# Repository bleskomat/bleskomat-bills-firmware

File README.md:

# bleskomat-bills-firmware

The Bleskomat Bills ATM is an offline Bitcoin Lightning Network ATM which accepts fiat bank notes and pays-out bitcoin. It's a great educational tool to give others a practical first experience with Bitcoin's Lightning Network.

You can buy the [Bleskomat Bills ATM](https://shop.bleskomat.com/product/bleskomat-bills-atm/) from the official Bleskomat shop. Alternatively, you can find all the components and equipment needed and build your own.

The Bleskomat Bills ATM must be paired with a server to facilitate Lightning Network payments on its behalf; see the options below:
* [Bleskomat Platform](https://platform.bleskomat.com) - non-custodial, requires a monthly subscription
* [bleskomat-server](https://github.com/bleskomat/bleskomat-server) - non-custodial, open-source, self-hosted solution
* [lnbits](https://github.com/lnbits/lnbits-legend) via the Bleskomat extension - open-source, self-hosted and possible to use custodial instances hosted by others; public instances of lnbits:
	* [legend.lnbits.com](https://legend.lnbits.com) - unstable, don't leave funds on this instance for very long

The rest of this document details the hardware and software requirements, how to build the hardware yourself, and instructions for compiling and uploading the firmware from source.

* [Requirements](#requirements)
	* [Hardware Requirements](#hardware-requirements)
	* [Software Requirements](#software-requirements)
* [Building the Hardware Device](#building-the-hardware-device)
	* [Prepare the breadboards](#prepare-the-breadboards)
		* [ESP32 devkit pinout](#esp32-devkit-pinout)
	* [Wiring the Power Supply](#wiring-the-power-supply)
		* [Optionally power the ESP32 devkit via 5V pin](#optionally-power-the-esp32-devkit-via-5v-pin)
	* [Wiring the E-Paper Module](#wiring-the-e-paper-module)
	* [Wiring the Button](#wiring-the-button)
	* [Wiring the Bill Acceptor](#wiring-the-bill-acceptor)
* [Installing Libraries and Dependencies](#installing-libraries-and-dependencies)
* [Compiling and Uploading to Device](#compiling-and-uploading-to-device)
* [Generate Font Header Files](#generate-font-header-files)
* [Configure Bill Acceptor](#configure-bill-acceptor)
* [Configuring the Device](#configuring-the-device)
	* [List of Configuration Options](#list-of-configuration-options)
	* [Browser-Based Configuration Tool](#browser-based-configuration-tool)
	* [Command-Line Configuration Tool](#command-line-configuration-tool)
	* [Hard-Coded Configuration](#hard-coded-configuration)
* [Changelog](#changelog)
* [Support](#support)
* [License](#license)
* [Trademark](#trademark)

## Requirements

This section includes information about the software and hardware requirements needed to build this project.

### Hardware Requirements

The following list includes all the parts needed to build the commercial Bleskomat ATM. The list includes direct links to suppliers of each part.

Basic components/equipment needed to build your own Bleskomat Bills ATM:
* 2 x breadboard (400-pin)
* Jumper wires (M-M)
* Jumper wires (M-F)
* ESP32 Devkit
* NV10 Bill Acceptor from Innovative Technologies
* WaveShare 4.2 inch E-Paper Module (b/w)
* Button
* 10k ohm resistor
* DC 5.5/2.1 mm DIP adapter
* 12V DC power adaptor (1.5A < 3A)
* Standard USB to micro USB cable

Optional components/equipment:
* Soldering iron
* 2.54 mm pins
* To power the ESP32 devkit from the 12V DC power supply:
	* XL4005 step-down converter
	* USB (F) adapter
	* Alternatively, you could use a USB car charger which includes both a step-down converter and USB (F) output

### Software Requirements

* [make](https://www.gnu.org/software/make/)
* [PlatformIO Core (CLI)](https://docs.platformio.org/en/latest/core/)
	* Version 6 or newer
	* Only the CLI ("Core") is required

## Building the Hardware Device

Before proceeding, be sure that you have all the project's [hardware requirements](#hardware-requirements).

### Prepare the breadboards

One breadboard is not large enough to accommodate all the pins of the ESP32 devkit due to the width of the devkit. This is why we recommend to connect two breadboards together.

Remove one of the power rails from one of the breadboards. Use the notches on the sides of the breadboards to connect them together length-wise.

Insert the ESP32 devkit into the pin holes of the new, combined breadboard.

Familiarize yourself with the ESP32 devkit's pinout reference below.

#### ESP32 devkit pinout

### Wiring the Power Supply

The first step to building the device is wiring the power supply. If already plugged in, __unplug__ the 12V DC power supply now. Connect the DC 5.5/2.1 end of the power supply to the DIP adapter. The positive (+) pins should be the power pins and the negative (-) pins should be the ground. You can use your multimeter to check in case you want to be extra safe:
* Plug-in the power supply to electricity
* Turn on your multimeter and set it to measure voltage in the appropriate range (probably 20V)
* Touch the __red__ lead of your multimeter to one of the positive pins
* Touch the __black__ lead of your multimeter to one of the negative pins
* If you see a negative voltage reading, swap the leads between the two wires
* The pin touched by the __black__ lead is the ground ("GND")
* The pin touched by the __red__ lead is the hot wire ("DC12V")
* Unplug the power supply again

Use a pair of M-F jumper wires to connect the DC 5.5/2.1 DIP adapter to one of the breadboard's power rails. Negative to negative, positive to positive. This rail will be your 12V DC power (positive) and the common ground (negative).

#### Optionally power the ESP32 devkit via 5V pin

If you'd like to make your Bleskomat build a little bit more portable, you can power the ESP32 devkit via its 5V pin. To do this you will need the XL4005 (or equivalent) step-down converter and the USB (F) adapter. Note that powering the ESP32 devkit via its micro USB port requires a regulated voltage of approximately 5V.

It's also possible to use a USB car charger in case you have an extra one lying around.

Connect the step-down converter's input pins to the 12V DC power rail and common ground using (M-F) jumper wires. Use a multimeter to measure the voltage at the out pins. In the case of the XL4005, use a small screwdriver to turn the screw on the little blue box. Turning the screw counter clockwise should lower the voltage, turning it the opposite direction should increase the voltage. Once you have the voltage set to 5V, connect the out pins to the center power rails of the breadboard. This will be your 5V DC power rail.

Use a soldering iron to solder four 2.54 mm pins to the USB (F) DIP adapter. Insert the pins directly into the breadboard wherever you have space available. Using (M-M) jumper wires, connect the negative and positive pins of the USB (F) DIP adapter to the 5V DC power rail.

Connect the negative pin of the 5V DC power rail to the negative of the 12V DC power rail to ensure that they share a common ground. This is important because without a common ground shared between the coin acceptor and ESP32 devkit, the ESP32 will not receive a clean signal from the coin acceptor.

Use a standard USB to micro USB cable to connect the USB (F) DIP adapter to the ESP32 devkit.

There are other options when powering the ESP32 - e.g via the 3.3V pin or the 5V/VIN pin. You should __never__ power the ESP32 via more than one of these options at the same time. For example, do not power the ESP32 via its 3.3V pin while also connecting the ESP32 via USB to your computer. This can damage the ESP32 and possibly also your computer.

### Wiring the E-Paper Module

Connect the E-Paper display module to the ESP32 using the following table as a guide:

| ESP32 | E-Paper Display Module |
|-------|------------------------|
| D25   | BUSY                   |
| D26   | RST                    |
| D27   | DC                     |
| D15   | CS                     |
| D13   | CLK                    |
| D14   | DIN                    |
| GND   | GND                    |
| 3.3V  | VCC                    |

Refer to the [ESP32 devkit pinout](#esp32-devkit-pinout) for help identifying the pins on your ESP32.

### Wiring the Button

Insert button pins into the breadboard wherever you have space available. Typically, its best to place the button at the center of a breadboard (over the gap).

Connect the button using the following table as a guide:

| ESP32    | Button    |
|----------|-----------|
| VIN (V5) | left pin  |
| GPIO33   | right pin |

Connect the right pin of the button to GND with a 10k ohm resistor.

Refer to the [ESP32 devkit pinout](#esp32-devkit-pinout) for help identifying the pins on your ESP32.

### Wiring the Bill Acceptor

This project supports the NV10 (USB+) and NV9 bill acceptors. The SIO protocol is used to communicate with the bill acceptor unit.

|  ESP32       | NV10/NV9 | Power Supply  |
|--------------|----------|---------------|
| GPIO16       | 1 (Tx)   |               |
| GPIO17       | 5 (Rx)   |               |
|              | 16       | - Ground      |
|              | 15       | + 12V DC      |

Refer to the [ESP32 devkit pinout](#esp32-devkit-pinout) for help identifying the pins on your ESP32.

## Installing Libraries and Dependencies

Before proceeding, be sure that you have all the project's [software requirements](#software-requirements).

Use make to install libraries and dependencies for the device firmware:
```bash
make install
```
* The firmware's dependencies are defined in its platformio.ini file located at `./platformio.ini`

If while developing you need to install a new library for the device firmware, use the following as a guide:
```bash
platformio lib install LIBRARY_NAME[@VERSION]
```
You can find PlatformIO's libraries repository [here](https://platformio.org/lib).

## Compiling and Uploading to Device

To compile the firmware (without uploading to a device):
```bash
make compile
```

To compile and upload to your device:
```bash
make upload DEVICE=/dev/ttyUSB0
```
The device path for your operating system might be different. If you receive a "Permission denied" error about `/dev/ttyUSB0` then you will need to set permissions for that file on your system:
```bash
sudo chown $USER:$USER /dev/ttyUSB0
```

To open the serial monitor:
```bash
make monitor DEVICE=/dev/ttyUSB0
```
Again the device path here could be different for your operating system.

## Generate Font Header Files

Each font used to render text on the E-Paper display is loaded from a C-style header file. If you need to add another font, expand the character set of an existing font, or add more font sizes; you will need to generate new font header files.

Have otf2bdf utility installed on your system - available via `apt-get` or `apt` on Ubuntu - e.g `apt-get install otf2bdf`.

Manually build bdfconv from source which is included along with this repository:
```sh
make bdfconv
```
Generate fonts:
```sh
make fonts
```
To manually generate fonts:
```sh
./scripts/generate-font-header-files.sh "/path/to/font/file.ttf" 2 32-382 16,20,24,28,32,36,40,44,48
```
* `2` - this is the build mode
	* "Font build mode, 0: proportional, 1: common height, 2: monospace, 3: multiple of 8". Examples:
		* CheckbookLightning = 1
		* Courier Prime Code = 2
* `32-382` - this is the character range (e.g. first character = 32, last = 382). More characters = larger header files.
* `6,7,8,9,10,12,14,16,18,20,22,24,28` - comma-separated list of font sizes

Generated font files are written to the ./include/fonts/u8g2 directory.

## Configure Bill Acceptor

Please refer to the following user manuals for detailed instructions regarding how to configure the NV10 (USB+) bill acceptor:
* [NV10 User Manual](docs/NV10-User-Manual-v1.1.pdf)

## Configuring the Device

It is possible to configure the device via the following methods:
* [Browser-Based Configuration Tool](#browser-based-configuration-tool)
* [Command-Line Configuration Tool](#command-line-configuration-tool)
* [Hard-Coded Configuration](#hard-coded-configuration)

### List of Configuration Options

The following is a list of possible configuration options:
* `apiKey.id` - The API key ID of the device. This is needed by the server to verify signatures created by the device.
* `apiKey.key` - The API key secret that is used to generate signatures.
* `apiKey.encoding` - The explicit encoding of the API key secret. This can be "hex", "base64", or empty-string (e.g "") to mean no encoding. When generating a new API key on the server, it will store the encoding along with the ID and secret.
* `callbackUrl` - The LNURL server base URL plus endpoint path. Example:
	* `https://p.bleskomat.com/u`
* `shorten` - Whether or not to shorten the LNURL; see the [lnurl-node module](https://github.com/chill117/lnurl-node#signed-lnurls) for more details.
* `uriSchemaPrefix` - The URI schema prefix for LNURLs generated by the device. It has been discovered that some wallet apps mistakenly only support lowercase URI schema prefixes. Uppercase is better because when encoded as a QR code, the generated image is less complex and so easier to scan. Set this config to empty-string (e.g `uriSchemaPrefix=`) to not prepend any URI schema prefix.
* `fiatCurrency` - The fiat currency symbol for which the device is configured; see [ISO 4217](https://en.wikipedia.org/wiki/ISO_4217).
* `fiatPrecision` - The number of digits to the right of the decimal point when rendering fiat currency amounts.
* `billValues` - The value of bills for which the bill acceptor has been configured. Each value separated by a comma. Integers and floating point (decimal) values are accepted. Examples:
	* CZK: `100,200,500,1000,2000,5000`
	* EUR: `5,10,20,50,100,200,500`
* `billTxPin` - The GPIO connected to the NV10/NV9's Tx pin.
* `billRxPin` - The GPIO connected to the NV10/NV9's Rx pin.
* `billBaudRate` - The baud rate of the SIO protocol communication with the NV10/NV9. This value will be `300` or `9600`.
* `logLevel` - Possible values:
	* `trace` - everything
	* `debug`
	* `info` - default
	* `warn`
	* `error`
	* `none` - nothing
* `webUrl` - The base URL for the web platform. If non-empty, it will be the base URL for:
	* `/intro?id=API_KEY_ID` - URL shown as a QR code on the instructions screen.
* `platformSockUri` - If the device is connected to WiFi and this value is non-empty, a WebSocket connection will be created to the provided URI. Example values:
	* `wss://platform.bleskomat.com/device` -  Uses TLS encryption, must provide the intermediate CA certificate. This can be saved to the device's SPIFFS file system via the [/serial](https://platform.bleskomat.com/serial) tool.
	* `ws://platform.bleskomat.com/device` - Unencrypted WebSocket
* `platformCACert` - The PEM-encoded CA certificate for the platform. This is used to create a secure (TLS) connection to the platform.
* `onlineOnly` - If set to `1` or `true`, then the ATM will only be enabled when connected to the platform.

### Browser-Based Configuration Tool

The Bleskomat Platform provides a [browser-based configuration tool](https://platform.bleskomat.com/serial) to upload pre-built device firmware, view real-time log output, update device configurations, run JSON-RPC serial commands, and more.

### Command-Line Configuration Tool

It is also possible to use the [bleskomat-cli](https://github.com/bleskomat/bleskomat-cli) command-line utility to communicate with a Bleskomat hardware device via JSON-RPC over serial API. Please refer to that project's readme for installation and usage information.

### Hard-Coded Configuration

Hard-coded configurations can be set by modifying the source file [config.cpp](https://github.com/bleskomat/bleskomat-bills-firmware/blob/master/src/config.cpp#L201).

Each time you make changes to the hard-coded configurations, you will need to re-compile and flash the ESP32's firmware.

## Changelog

See [CHANGELOG.md](https://github.com/bleskomat/bleskomat-bills-firmware/blob/master/CHANGELOG.md)

## Support

Need some help? Join us in the official [Telegram group](https://t.me/bleskomat) or send us an email at [support@bleskomat.com](mailto:support@bleskomat.com) and we will try our best to respond in a reasonable time. If you have a feature request or bug to report, please [open an issue](https://github.com/bleskomat/bleskomat-bills-firmware/issues) in this project repository.

## License

The project is licensed under the [GNU General Public License v3 (GPL-3)](https://tldrlegal.com/license/gnu-general-public-license-v3-(gpl-3)):
> You may copy, distribute and modify the software as long as you track changes/dates in source files. Any modifications to or software including (via compiler) GPL-licensed code must also be made available under the GPL along with build & install instructions.

## Trademark

"Bleskomat" is a registered trademark. You are welcome to hack, fork, build, and use the source code and instructions found in this repository. However, the right to use the name "Bleskomat" with any commercial products or services is withheld and reserved for the trademark owner.

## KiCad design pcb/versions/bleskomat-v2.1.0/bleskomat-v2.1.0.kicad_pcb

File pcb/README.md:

# Bleskomat PCB

In order to make Bleskomat easy to reproduce in a consisten way and compress most of the cable complexity we are building this PCB. This PCB aims to connects all the component that are required for Bleskomat between them and with the microcontroler ESP32.

## Requirements
- [kiCad](https://kicad-pcb.org/)

## Resources to learn
### PCB building
- [An Intro to KiCad](https://www.youtube.com/watch?v=vaCVh2SAZY4&list=PL3bNyZYHcRSUhUXUt51W6nKvxx2ORvUQB)
  - It uses an older version of KiCad but still good
- [Tutorials](https://kicad-pcb.org/help/tutorials/)
- [Similar project](https://github.com/RuiSantosdotme/ESP32-Weather-Shield-PCB)

### Power connectors
- [What to do with third contact in DC barrel plug with only two input contacts](https://electronics.stackexchange.com/questions/90529/what-to-do-with-third-contact-in-dc-barrel-plug-with-only-two-input-contacts)
- [How to Select a Dc Power Connector](https://www.cuidevices.com/blog/how-to-select-a-dc-power-connector)

## Resources footprints

- [Kicad footprints](https://kicad.github.io/footprints/)
- [ultralibrarian -Kicad footprints and symbols](https://www.ultralibrarian.com/)

## PCB CAD Program

For designing the Bleskomat PCB we are using KiCad, it is a multiplatform and open source software to design PCBs.
Kicad is a set of multiple programs that work together in order to design a PCB. The process to follow when creating PCB is described in [Process](#process)

- eeSchema – a schematic capture program
- Library Editor – a program to create schematic symbols
- PCBnew – a PCB layout tool
- Footprint Editor – a program to create PCB footprints
- CvPcb is a tool that allows you to associate components in your schematic to component footprints used when laying out the printed circuit board.
- Gerbview – a program to inspect Gerber files

### Process of working in KiCad

1. Design circuit
This process is when you design you circuit in paper and maybe also build it using breadboard and jupmer cables. In this process you should find your components from a compnent's provider and if they have, collect also symbols and footprints from them.
2. Create schematic Symbol (Symbol Library Editor)
If you did not find symbol for some of the selected components you can create it with this editor in KiCad.
3. Schematic capture (eeSchema)
Once you have defined your circuit (and test it), you use this program to tell KiCad how all the componets are connected to each other. This is just logic, it is not the phisical representation.
4. Create footprints (Footprint Editor)
If you did not find footprints for some of the selected components you can create it with this editor in KiCad.
5. Generate netlist (CvPcb)
You generate netlist when you connect the symbols that you used in `eeSchema` with the footprints that each component is going to have.
6. Board layout (PCBnew)
Once you have fininished the previous steps you can click on update PCB in the program `PCBnew` and you will see all the components with wire lines of how they need to be connected.
7. Production (Gerbview)
This will produce the one file per each of the layers that the PCB is going to have.
8. BOM (Bill of Material)
Once you have finshed everything you can generate you BOM file. This file can be in different formats, we are using `csv`. You can generate this file if you click on `Generate Bill of Material` in the program `eeSchema` and use the script `bom2csv` like:
`xsltproc -o "%bleskomat-bom-v2.1.csv" "/usr/share/kicad/plugins/bom2csv.xsl" "%I"`.
9. Centroid/ Pick & Place file is a file with extension `.pos` that is required sometimes by the manufacturer to assembly automatically.
  - https://www.pcbway.com/helpcenter/technical_support/Generate_Position_File_in_Kicad.html
  - https://electronics.stackexchange.com/questions/456671/kicad-no-footprint-for-automated-placement
  A.Set the origin point
    Select the menu bar Place-> Drilling and Position Offset, place the origin at the bottom left corner of the PCB board frame, and then place [Layer Alignment Mark] to the position of the origin just placed.
  B.Generate Footprint Position File
    Click the menu [File] >> [Fabrication Output] >> [Footprint Position (.pos) File], select the output directory, other default, click [Generate Position File]. Open the package location file with Notepad or text editor. You can see the contents have reference number, value, package, X Y coordinate, orientation, board surface, etc.

    The checkbox 'Include footprints with SMD pads even if not marked Surface Mount' should be selected.

### KiCad design rules

- [oshpark](https://docs.oshpark.com/design-tools/kicad/kicad-design-rules/)

## Trace width calculator

- [4pcb trace width calculator](https://www.4pcb.com/trace-width-calculator.html)

For power -> 0.762 mm (30 mils)

## List of Components

Detailed list of components to be mounted on the PCB:

* epaper
  * 8 pins
  * https://www.digikey.com/en/products/detail/jst-sales-america-inc/B8B-XH-A-LF-SN/1651049
  * Symbol and footprint -> https://app.ultralibrarian.com/details/FA962F68-295C-11EA-A124-0AD2C9526B44/JST/B8B-XH-A--LF--SN-?ref=digikey

* Button connector
  * 2 pins
  * https://www.digikey.com/en/products/detail/jst-sales-america-inc/B2B-XH-A-LF-SN/1651045
  * Symbol and footprint -> https://app.ultralibrarian.com/details/7D7B9D86-5525-11E9-AB3A-0A3560A4CCCC/JST/B2B-XH-A-LF--SN-?ref=digikey

* Coin acceptor connector
  * 5 pins
  * https://www.digikey.com/en/products/detail/jst-sales-america-inc/B5B-XH-A-LF-SN/1530483
  * Symbol and footprint -> https://app.ultralibrarian.com/details/CFF72197-B726-11E9-AB3A-0A3560A4CCCC/JST/B5B-XH-A--LF--SN-

* NV9/10 bill acceptor connector
  * Socket to be soldered on the PCB:
    * https://www.digikey.com/en/products/detail/3m/30316-6002HB/1237397
    * Symbol and footprints -> https://app.ultralibrarian.com/details/B982199F-7F64-11EA-8C00-0AD2C9526B44/3M/30316-6002HB?ref=digikey

* Button resistor
  * 10K ohm
  * https://www.digikey.com/en/products/detail/yageo/CFR-25JB-52-10K/338
  * Symbol and footprint -> https://app.ultralibrarian.com/details/C2AE6AA6-1080-11E9-AB3A-0A3560A4CCCC/Yageo/CFR-25JB-52-10K

* Step down converter
  * 4 pins
  * Instead of using the step-down converter board/module, we can mount a single step-down converter component which outputs the exact voltage we know we want (3.3V at max. 500mA):

    * https://www.digikey.com/en/products/detail/recom-power/R-78E3-3-1-0/5327711
    * Symbol and footprint -> https://www.snapeda.com/parts/R-78E3.3-1.0/RECOM%20POWER%20GMBH/view-part/?ref=digikey

* 12V socket
  * 3 pins
  * https://www.digikey.com/en/products/detail/cui-devices/PJ-202A/252007
    * Footprint -> https://github.com/Digi-Key/digikey-kicad-library/blob/master/digikey-footprints.pretty/Barrel_Jack_5.5mmODx2.1mmID_PJ-202A.kicad_mod
* SDcard connector
  * https://www.digikey.com/en/products/detail/hirose-electric-co-ltd/DM3D-SF/1786510
  * Symbol and footprint -> https://app.ultralibrarian.com/details/2CC8D729-C606-11E9-AB3A-0A3560A4CCCC/Hirose/DM3D-SF?ref=digikey&open=exports&exports=KiCAD

* LED
  * https://www.digikey.com/en/products/detail/lite-on-inc/LTST-C194TBKT/2356225
  * Symbols and footprint -> https://www.snapeda.com/parts/LTST-C194TBKT/Lite-On%20Inc./view-part/?ref=digikey

* ESP32-WROOM-32SE
  * https://www.digikey.com/en/products/detail/espressif-systems/esp32-wroom-32-8mb/9381712
    * Symbol and footprint -> https://app.ultralibrarian.com/details/D182CFF0-E9AE-11E9-B85E-0AD2C9526B44/Espressif-Systems/ESP32-WROOM-32--8MB-?ref=digikey

* Firmware connector
  * 6 pins - to connect to this -> https://www.olimex.com/Products/IoT/Programmer/ESP-PROG/open-source-hardware
  * https://www.digikey.com/en/products/detail/jst-sales-america-inc/B6B-XH-A-LF-SN/1000381
  * Symbols and footprint -> https://app.ultralibrarian.com/details/7681E56E-AA22-11E9-AB3A-0A3560A4CCCC/JST/B6B-XH-A-LF--SN-?ref=digikey

* Switch to select source of power:
  * https://www.digikey.com/en/products/detail/c-k/JS202011CQN/1640097 - middle pins will connect to the ESP32's 3V3 pin
  * Symbol and footprint -> https://app.ultralibrarian.com/details/57BD9AFF-2115-11E9-AB3A-0A3560A4CCCC/C-K/JS202011CQN?ref=digikey

## Circuit boot and flash mode

When booting ESP32 if GPIO0 is high, the device will normal boot while if GPIO0 is low, it will boot into flash mode allowing us to upload a new application into the device's flash storage.
We create the circuit below to allow us to boot and boot into flash mode in an easly way.

* Boot button circuit

When pin `EN` is set to low ESP32 is rebooting. This can be used for debugging to start the program from the beginning or for setting ESP32 into flash mode in combination with `Flash button`.

* Flash button circuit

When pressing the button GPIO0 is set to low and therefore when booting if the button is pressed, the microcontroler knows that we want to boot in flash mode.

## Communication with custom PCB

When building our own PCB, for sake of simplicity we are not including the USB to UART communications part so we use those parts as separate modules that we can connect to our PCB when we need to update (flash) firmware or listen to serial outputs communication for debugging. For connecting to our PCB we have created "Firmware connector" that exposes the ESP32 pins that are required to connect to separated USB to UART external component. Below you can see a list of those USB to UART components:

* [CP2102 GME USB-UART, RESET pin](https://www.gme.cz/prevodnik-usb-uart-reset-pin-product-38325)
  * Definitely your best option
  * It has LEDs that tell you if it is connected and if there is communication going to TXD or RXD. Very helpful.
* [OLIMEX ESP-PROG](https://www.olimex.com/Products/IoT/Programmer/ESP-PROG/open-source-hardware)
  * It does not have any LED to let you know if something is happening

### Wiring USB-UART with ESP32

|  ESP32      | USB-UART |
|-------------|----------|
| TX0         | RX       |
| RX0         | TX       |
| GND         | GND      |
| 3.3V        | 3.3V     |

### Flashing ESP32

Whether you are using a PCB that has include buttons for flashing and boot or you use a PCB without it and build the [circuit](#circuit-boot-and-flash-mode) as separate part to change to flash mode: hold the "EN" button down while pressing and releasing "Boot" while you are running `make upload`

### Listenig to serial monitor

When connecting the USB-UART component to the PCB and your computer you can listen to serial monitor as usualy using `make monitor`.

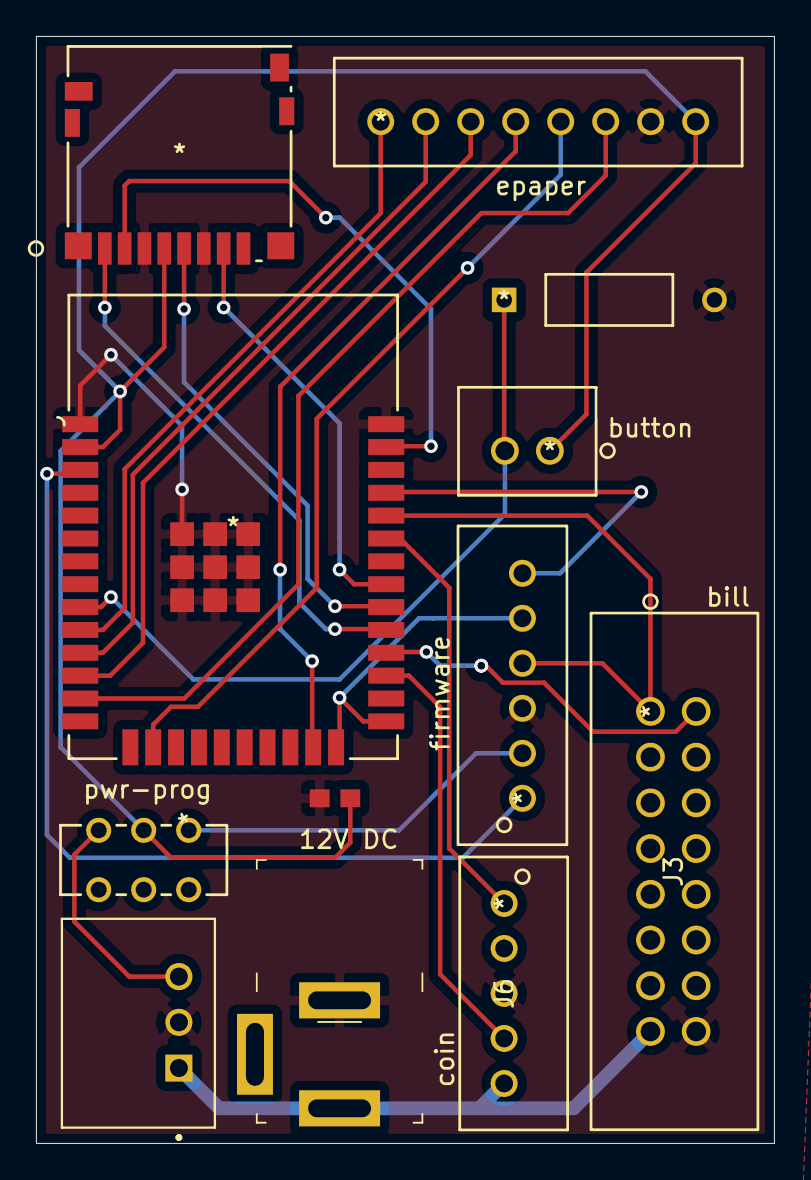
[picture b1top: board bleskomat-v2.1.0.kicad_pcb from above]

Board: 2 copper layers, 41.0 x 61.5 mm, 12 parts (0 on the bottom side), 23 nets.

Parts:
12V DC: 12V-SOCKET; Barrel_Jack_5.5mmODx2.1mmID_PJ-202A
D1: LED-LTST-C194TBKT; 0603
J1: firmware; B6B-XH-ALFSN
J2: epaper; B8B-XH-A LFSN
J3: bill; 30316-6002HB
J4: button; B2B-XH-ALFSN
J5: SD_CARD; DM3D-SF
J6: coin; B5B-XH-A LFSN
PS1: step-down-R-78E3.3-1.0; CONV_R-78E3.3-1.0
R1: R 10K; CFR-25JB-52-10K
U1: ESP32-WROOM-32_8MB; ESP32-WROOM-32 8MB
U2: switch power JS202011CQN; JS202011CQN

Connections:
GND: 12V DC.2, D1.1, J1.3, J2.7, J3.16, J5.3, J5.6, J6.3, PS1.2, R1.2, U1.1, U1.38, U1.39, U1.40, U1.41, U1.42, U1.43, U1.44, U1.45, U1.46, U1.47
unnamed: D1.2, J2.8, J4.1, J5.4, U1.2, U2.2
unnamed: J1.1, U1.3
unnamed: J1.2, U2.1
unnamed: J1.4, J3.1, U1.34
unnamed: J1.5, U1.24, U1.25
unnamed: J1.6, U1.35
unnamed: J2.1, U1.10
unnamed: J2.2, U1.11
unnamed: J2.3, U1.12
unnamed: J2.4, U1.23
unnamed: J2.5, U1.16
unnamed: J2.6, U1.13
unnamed: J3.2, U1.28
unnamed: 12V DC.1, J3.15, J6.5, PS1.1
unnamed: J4.2, R1.1, U1.9
unnamed: J5.1, U1.29
unnamed: J5.2, U1.37
unnamed: J5.5, U1.30
unnamed: J5.7, U1.31
unnamed: J6.1, U1.33
unnamed: J6.4, U1.27
unnamed: PS1.3, U2.3

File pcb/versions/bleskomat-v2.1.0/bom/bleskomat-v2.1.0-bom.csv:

Reference, Value, Footprint,URL, MANUFACTURER, MAXIMUM_PACKAGE_HEIGHT, PARTREV, STANDARD
U1,ESP32-WROOM-32_8MB,bleskomat-footprints:ESP32-WROOM-32 8MB,https://www.digikey.com/en/products/detail/espressif-systems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,,,,
J2,epaper B8B-XH-A_LFSN,bleskomat-footprints:B8B-XH-A LFSN,https://www.digikey.com/en/products/detail/jst-sales-america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,,,,
J4,button B2B-XH-ALFSN,bleskomat-footprints:B2B-XH-ALFSN,https://www.digikey.com/en/products/detail/jst-sales-america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,,,,
J6,coin acceptor B5B-XH-A_LFSN,bleskomat-footprints:B5B-XH-A LFSN,https://www.digikey.com/en/products/detail/jst-sales-america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,,,,
J3,NV9 30316-6002HB,bleskomat-footprints:30316-6002HB,https://www.digikey.com/en/products/detail/3m/30316-6002HB/1237397,,,,
R1,R 10K button,bleskomat-footprints:CFR-25JB-52-10K,https://www.digikey.com/en/products/detail/yageo/CFR-25JB-52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,,,,
PS1,step-down-R-78E3.3-1.0,bleskomat-footprints:CONV_R-78E3.3-1.0,https://www.digikey.com/en/products/detail/recom-power/R-78E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,RECOM,10.40mm,6,Manufacturer Recommendations
J5,SD_CARD_HOLDER_DM3D-SF,bleskomat-footprints:DM3D-SF,https://www.digikey.com/en/products/detail/hirose-electric-c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,,,,
U2,switch power JS202011CQN,bleskomat-footprints:JS202011CQN,https://www.digikey.com/en/products/detail/c-k/JS202011CQN/1640097 ,,,,
D1,LED-LTST-C194TBKT,bleskomat-footprints:0603,https://www.digikey.com/en/products/detail/lite-on-inc/LTST-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,,,,
J1,firmware B6B-XH-ALFSN,bleskomat-footprints:B6B-XH-ALFSN,https://www.digikey.com/en/products/detail/jst-sales-america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,,,,
POWER1,12V-SOCKET,bleskomat-footprints:Barrel_Jack_5.5mmODx2.1mmID_PJ-202A,https://www.digikey.com/en/products/detail/cui-devices/PJ-20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,,,,

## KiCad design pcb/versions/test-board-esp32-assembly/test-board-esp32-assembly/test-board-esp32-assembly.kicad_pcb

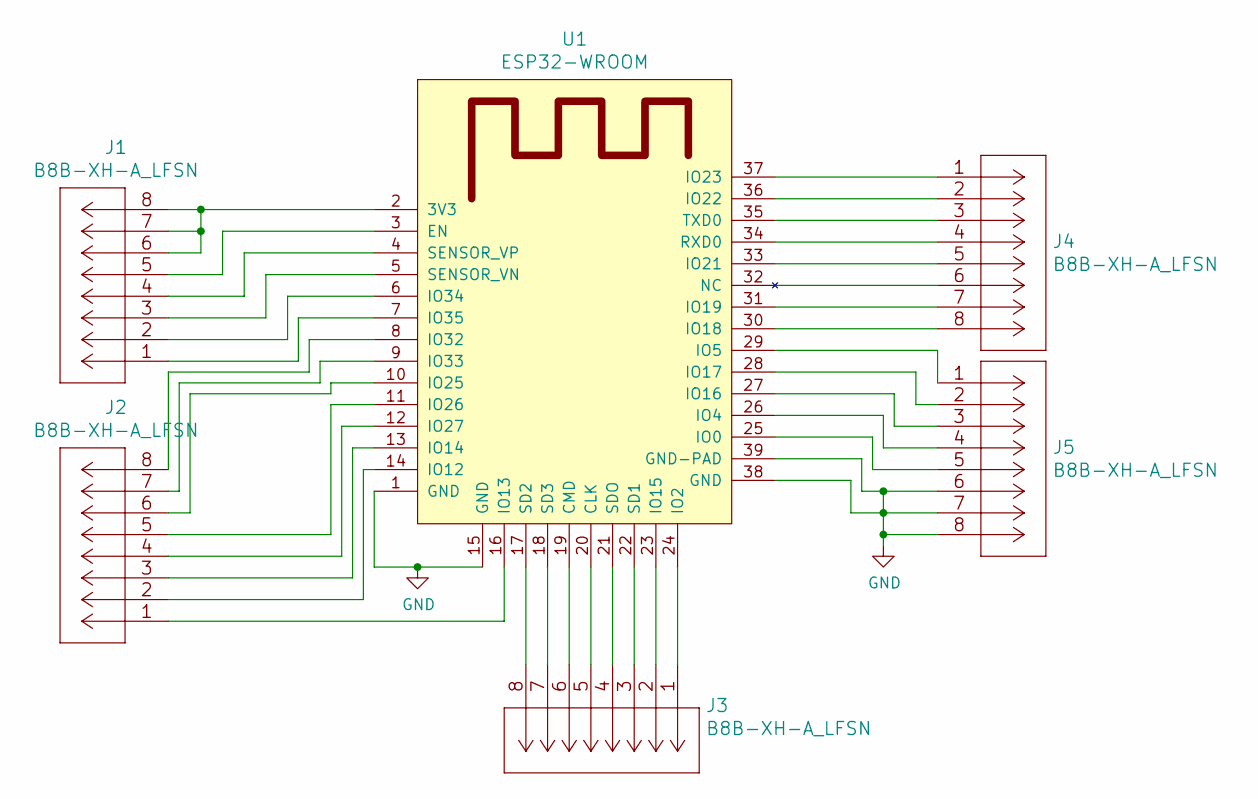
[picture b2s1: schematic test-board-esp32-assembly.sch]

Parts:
J1, J2, J3, J4, J5: B8B-XH-A_LFSN; B8B-XH-A LFSN
U1: ESP32-WROOM

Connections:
GND: J5.6, J5.7, J5.8, U1.1 (GND), U1.15 (GND), U1.38 (GND), U1.39 (GND-PAD)
unnamed: J1.1, U1.7 (IO35)
unnamed: J1.2, U1.6 (IO34)
unnamed: J1.3, U1.5 (SENSOR_VN)
unnamed: J1.4, U1.4 (SENSOR_VP)
unnamed: J1.5, U1.3 (EN)
unnamed: J1.6, J1.7, J1.8, U1.2 (3V3)
unnamed: J2.1, U1.16 (IO13)
unnamed: J2.2, U1.14 (IO12)
unnamed: J2.3, U1.13 (IO14)
unnamed: J2.4, U1.12 (IO27)
unnamed: J2.5, U1.11 (IO26)
unnamed: J2.6, U1.10 (IO25)
unnamed: J2.7, U1.9 (IO33)
unnamed: J2.8, U1.8 (IO32)
unnamed: J3.1, U1.24 (IO2)
unnamed: J3.2, U1.23 (IO15)
unnamed: J3.3, U1.22 (SD1)
unnamed: J3.4, U1.21 (SDO)
unnamed: J3.5, U1.20 (CLK)
unnamed: J3.6, U1.19 (CMD)
unnamed: J3.7, U1.18 (SD3)
unnamed: J3.8, U1.17 (SD2)
unnamed: J4.1, U1.37 (IO23)
unnamed: J4.2, U1.36 (IO22)
unnamed: J4.3, U1.35 (TXD0)
unnamed: J4.4, U1.34 (RXD0)
unnamed: J4.5, U1.33 (IO21)
unnamed: J4.6, U1.32 (NC)
unnamed: J4.7, U1.31 (IO19)
unnamed: J4.8, U1.30 (IO18)
unnamed: J5.1, U1.29 (IO5)
unnamed: J5.2, U1.28 (IO17)
unnamed: J5.3, U1.27 (IO16)
unnamed: J5.4, U1.26 (IO4)
unnamed: J5.5, U1.25 (IO0)

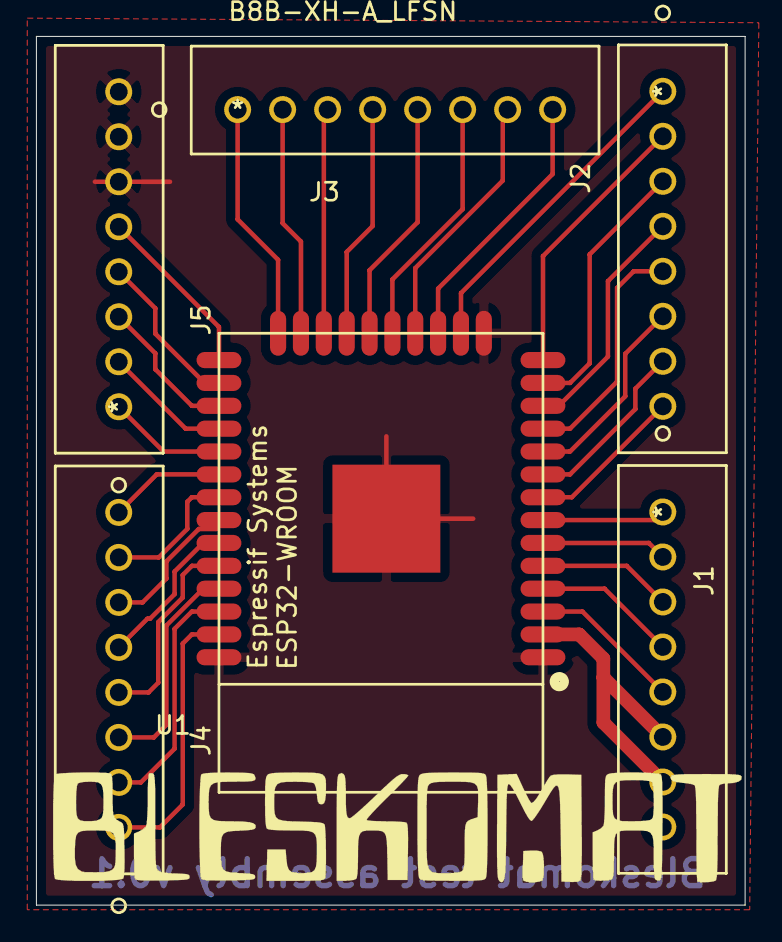
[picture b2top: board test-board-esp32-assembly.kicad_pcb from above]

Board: 2 copper layers, 39.4 x 48.3 mm, 6 parts (0 on the bottom side), 36 nets.

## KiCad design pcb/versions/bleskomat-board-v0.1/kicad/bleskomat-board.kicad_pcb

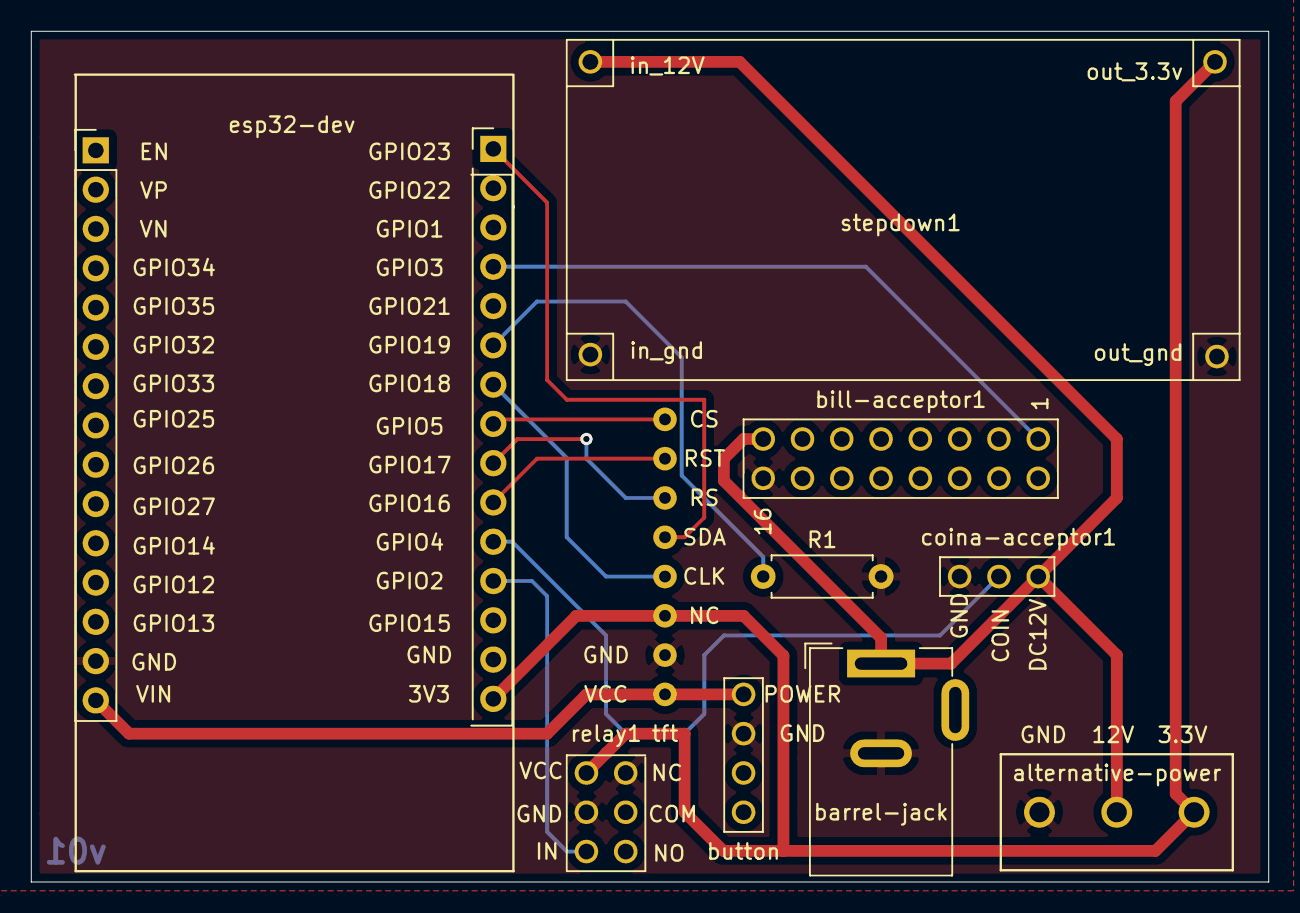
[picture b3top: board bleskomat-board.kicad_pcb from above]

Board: 2 copper layers, 80.0 x 55.0 mm, 10 parts (0 on the bottom side), 13 nets.

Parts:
R1: 10k; R_Axial_DIN0207_L6.3mm_D2.5mm_P7.62mm_Horizontal
alternative-power: Screw_Terminal_01x03; TerminalBlock_5mm
barrel-jack: 12V-SOCKET; BarrelJack_Wuerth_6941xx301002
bill-acceptor1: billacceptor-connector
button: button; button-connector
coina-acceptor1: coinacceptor-connector
esp32-dev: esp32; ESP32_Devkit_DOIT_V2
relay1: relay-connector; relay-temporary-connector
stepdown1: stepdown-connector; stepdown
tft: tft-connector

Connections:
GND: R1.2, alternative-power.1, barrel-jack.2, bill-acceptor1.16, button.2, coina-acceptor1.3, esp32-dev.14, relay1.3, relay1.5, stepdown1.1, stepdown1.3, tft.7
unnamed: alternative-power.2, barrel-jack.1, bill-acceptor1.15, coina-acceptor1.1, stepdown1.2
unnamed: alternative-power.3, esp32-dev.16, relay1.6, stepdown1.4, tft.6
unnamed: R1.1, esp32-dev.25
unnamed: button.1, esp32-dev.15, tft.8
unnamed: esp32-dev.19, relay1.4
unnamed: coina-acceptor1.2, esp32-dev.20
unnamed: esp32-dev.21, tft.2
unnamed: esp32-dev.22, tft.3
unnamed: esp32-dev.23, tft.1
unnamed: esp32-dev.24, tft.5
unnamed: bill-acceptor1.1, esp32-dev.27
unnamed: esp32-dev.30, tft.4

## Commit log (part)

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2020-01-20 feat: coin acceptor 616 communication
2020-01-20 add README.md file
2020-01-23 Bleskomat signature with coin acceptor
2020-01-26 docs: getting started with esp32
2020-01-26 docs: tft screen cable mapping
2020-02-13 fix: move hmac sign to util
2020-02-19 fix: improve qrcode size
2020-02-22 TFT/ESP32 were flipped for most pins in table
2020-02-23 Refactor, follow flow as described by issue #17
    Display accumulated fiat value
2020-04-15 3D model for Dell PC box
2020-04-15 Mark "vendored" files for calculating project code percentages
2020-05-04 feat: button to qrcode generation and clear
2020-05-06 (un-)licensed info
2020-05-15 Configurable build, platformio
2020-05-18 Don't require config.json file for dummy build flags
2020-05-21 Refactor: logs, display, config
2020-05-22 Proper escaping for string literals as build flags
2020-05-22 Smaller font, calculate real text width/height (no magic constants)
2020-05-22 Refactor to support bill or coin acceptor
2020-05-23 Indentation fix
2020-05-23 Remove un-used code from utilstrencodings
2020-05-26 Updated readme w/ more detailed hardware list
2020-05-26 esp32-wroom data sheet
2020-05-26 Bill acceptor (NV10) manual
2020-05-30 Bleskomat w/ coin acceptor wiring schematic
2020-06-03 private:true to prevent accidental publish
2020-06-03 Change cmd from load to init (better naming)
2020-06-09 feat: bill acceptor integratio module
2020-06-10 parts list spreadsheet
2020-06-19 Working implementation
2020-06-23 Stencils (logo, bitcoin-lightning)
2020-06-24 case measurements
2020-06-24 training coin acceptor section
2020-06-25 saving gcode in git not so useful
2020-06-25 bitcoin-lightning stencil stl files
2020-07-04 feat: button integration
2020-07-15 Countdown timer
2020-07-20 Refactor module inclusion
2020-07-20 Button refactor
    Don't render QR code while still counting coins
    Clear QR code when button pressed (if QR code displayed)
2020-08-04 Coin acceptor with relay module
2020-08-04 Removed unused function "getTimeSinceLastInserted"
2020-08-04 Promotional image of bleskomat being used
2020-08-04 Updated hardware requirements list
2020-08-05 Latest wiring diagram
2020-08-05 Updated readme w/ latest wiring diagram
2020-08-06 Added NV10 to hardware list
2020-08-06 Fix alignment of coin acceptor pins
2020-08-06 Set baud rate for serial monitor to standard 115200
2020-08-07 Fixup readme (wiring instructions)
2020-08-07 Instructions for wiring the step-down converter
2020-09-01 Stickers: instructions, logo
2020-09-18 resized instructions sticker
2020-09-26 Updated wiring diagram
2020-09-26 Removed unnecessary extra wiring diagram
2020-09-28 Print full error stack trace, wait for db ready
2020-09-28 Updated deps
2020-11-04 Moved lnurl encoding, signing to separate lib
    Added header guards
2020-11-15 Load config from SD card
    Wiring of SD card explained in readme
    Generate bleskomat.conf file with `npm run print:config` task
2020-11-18 Store config in non-volatile storage (NVS) (flash memory)
2020-12-04 Added "transactionLimit" config, minor refactor
2020-12-04 Use e-paper display module instead of TFT
    SD card SPI module added
    Splash screen (BLESKOMAT + slogan)
    Instructions screen
    Insert fiat screen (amount + symbol)
    Transaction complete screen (QR code + instruction)
    Added custom fonts, script and instructions to build more
2020-12-09 Version number provided as config, printed to serial monitor and log
2020-12-20 feat: new coin acceptor dg600f
2020-12-21 Working with epaper
2020-12-24 Provide bank note values as new config: "billValues"
2020-12-24 Firmware version number, commit hash now printed to serial monitor and debug log file
2020-12-28 add nv9 documentation
2020-12-28 docs: change case designes in svg
2020-12-30 Fix crashing caused by empty billValues config
2020-12-30 Set coin acceptor A4 param to 03 for 3 bytes (title, coin, xor)
2020-12-30 fiatPrecision is an integer, CZK billValues, higher tx limit
2020-12-30 fix: add fiatPrecission to configs
2021-01-02 Configuration options explained
2021-01-02 New config "uriSchemaPrefix"
2021-01-02 Append API key ID to instructions web URL
2021-01-03 Fix render amount text by stepping down font size
2021-01-03 Add "push button to start" text to splash screen
2021-01-03 Disallow inserting coins if possible to exceed tx limit
2021-01-03 Instructional sticker not needed anymore
2021-01-06 fix: change bill acceptor pins so it works
2021-01-07 feat: case screen frame
2021-01-14 Only turn off coin acceptor when buyLimit > 0 and not already off
2021-01-14 fix: change transactionLimit to buyLimit (#85)
    * fix: change transactionLimit to buyLimit
    * Only turn off coin acceptor when buyLimit > 0 and not already off
2021-01-15 Reprogramming NV9 with VirtualBox, Win8 VM
2021-01-17 Removed out-dated wiring diagram from readme
    Added note that it needs to be updated with latest components.
2021-01-17 Updated list of hardware parts, suppliers
2021-01-18 Minor changes in troubleshooting nv9/10
2021-01-18 feat: disable bill acceptor (#69)
    * feat: disable bill acceptor
    * fix: change bill acceptor pins so it works
2021-01-21 feat: reject bills after buyLimit
2021-01-25 Fixup VM instructions
2021-01-31 Updated lnurl platformio
2021-02-01 Standardize NV9 options
2021-03-08 ESP programmer docs, esp32 pinout image
2021-03-10 SD card pinout
2021-03-17 feat: pcb test for assembly
2021-03-21 Dummy screen module
2021-03-22 Commented code to override config options
2021-04-09 pcb: add centroid pick and place file
2021-04-14 adds instruction to take photo for the records on transaction complete screen
2021-04-15 include a function to fetch exchange rate and process the Json
    Enable it by `-D FETCH_EXCHANGE_RATE` compilation flag (within the
    platformio.ini file). This however causes the memory exhaustion. To
    overcome it and allow testing you disable some modules (e.g. coin
    accceptor and screen).
2021-04-16 Adds default for the flash partitioning
    $ cp ~/.platformio/packages/framework-arduinoespressif32/tools/partitions/default.csv .
2021-04-16 increasing the flash partition for the firmware
2021-04-19 feat: pcb boot and flash circuits
2021-04-21 when the exchange rate is available, include it in lnurl
2021-04-26 Display 7 words on transaction complete screen
    New optional config referencePhrase is device 2-word unique identifier
2021-04-26 Fix precision of buyLimit on insert fiat screen
    Re-align insert fiat screen
2021-04-27 Added disabled screen
2021-04-28 Perform status check HTTPS request on boot and once per 5 minutes
    Update the configurations in memory and NVS
    Show/hide disable screen when enabled config changes
2021-04-29 Change DER to PEM
2021-05-06 Websockets instead of HTTP polling for device options
    Can receive device options, exchangeRate from server
    Authorization challenge signature (HMAC-SHA256) when initializing socket
2021-05-09 Add install platform to make
2021-05-24 Move assets/docs to more appropriate repos
    Added fonts that are used in the firmware
    General clean-up
2021-05-25 Renamed vendor manuals
2021-05-25 Renamed doc files
2021-06-04 Localization
    UTF-8 support via u8g2
    New font header files because u8g2 uses a different font format
    Cleaned up assets/fonts, added sfd and otf formats for fonts
    Splash and instructions screens now rendered as text without images
    Use full window render mode with partial updates, much faster
2021-06-04 Put comments back
2021-06-09 Added german localization strings
2021-06-09 Additional notes for platformio requirement
2021-06-11 Added button wiring instructions
2021-06-13 Minor optimization to reduce file reads
2021-06-14 Fix issue 130 - QR code scanning problem
2021-06-15 Fix issue 59: SD card read/write errors when epaper SPI connected
2021-06-25 fix: when disable screen acceptors should disable
2021-06-25 Move new disable/enableAcceptors methods to modules
2021-07-04 Clarify build flag, pin naming for bill/coin acceptors
2021-07-23 Fix QR code margin problem when display inside case
2021-07-29 Comment the hard-coded enabled config
2021-10-06 fix: remove apiKey.key from logs
2021-10-23 The SD card should be automatically re-mounted at loop
    There was a logic error in the if statement
2021-10-23 fix: mounting sdcard after change screen (#141)
    * fix: mounting sdcard after change screen
    * The SD card should be automatically re-mounted at loop
    There was a logic error in the if statement
2022-01-12 Added changelog
2022-01-12 Added release directory
2022-03-31 Change samotari to bleskomat
2022-05-02 Firmware version build flag, var
    Print apiKey.key config key, but XXX instead of value
2022-05-23 Refactor config and modules
    Memory (RAM) usage improvements
2022-05-24 Use fixed version numbers: platform, framework
2022-05-24 Version
2022-05-24 Changelog in readme
2022-05-27 Safer use of map.at
    Better name for map char* comparator
2022-05-27 Use SPIFFS to save log files
    Improved logging
    Button delay: Remove delay(), use elapsed time check instead
2022-05-29 Improve logging and error handling in JSON-RPC
2022-05-30 Fixup online mode
    Removed ping-server code
    Simplified platform code
    Fix TLS CA cert usage
2022-05-31 Simplify network.cpp (wifi) log messages
    Keep platformSockUri in-memory
2022-05-31 Bill: Cleaner logging, handle case where note rejected
    Enable escrow timeout
2022-05-31 Simplify SD card usage
2022-05-31 Changelog
2022-06-03 Added spiffsFormatted config flag
    Return spiffsInitialized flag in getinfo JSON-RPC command
    Send response for restart JSON-RPC command
2022-06-03 Fix getInt/Short/Float config value when set to empty-string
2022-06-08 Checkbook -> Bleskomat font
2022-06-13 Better initialization state handling
2022-07-06 Refactor i18n lang strings
2022-07-06 Added release v1.3.4 firmware.bin
2023-02-07 fix(locale): remove coins from locale
2023-02-08 Remove coin acceptor code, documentation, etc
2023-02-09 fix(bill-acceptor): wait for escrow mode confirmation
2023-02-09 Debounce enable escrow commands
2023-02-09 Fix debounce of enable escrow command
2023-03-14 chore(config): update default fiatPrecision to 0
2023-04-03 Added bleskomat atm firmware v1.4.0
2023-04-04 Version and firmware name
2023-04-14 feat: cache for restoring state
2023-04-14 feat: cache for restoring state (#159)
    * feat: cache for restoring state
    * Make cache usage easier
    ---------
2023-04-15 Put SD card related info back in README
2023-04-15 chore(README): remove SDcard from README
2023-04-16 Clean-up readme
    Add open-source license
    Add instructions to build hardware
    Fixup make fonts
2023-04-20 Ping, reconnect with bill acceptor
2023-04-22 Added code, documentation for DG600F coin acceptor
2023-04-29 Remove opensans font
    Fixup font rendering on all screens
2023-05-22 Version, minor readme fixup, remove un-used line in config
2023-06-21 Wait JSON-RPC to time-out before init e-paper, bill acceptor
2023-06-27 Update changelog
2023-06-28 feat: update json-rpc to receive bluetooth messages
2023-07-02 feat: start bluetooth only when button is pressed at start up
2023-07-02 feat: add ble initialization
2023-07-12 config: add possibility to reset display/hide qr code after some time, default - do not hide it
2023-08-20 fix(json-rpc): removed non-existing method definition
2023-08-20 fixup! feat: bluetooth full support JSON RPC send and receive
2023-11-21 Added waiting to connect screen
2024-02-14 feat: when waitingToConnect screen inhibit billAcceptor
2024-05-28 fix: when params is empty array returns full config
2024-06-05 fix: when params is empty array returns full config (#163)
    * fix: when params is empty array returns full config
    * Fix minor syntax error
    ---------

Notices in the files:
README.md:
The project is licensed under the [GNU General Public License v3 (GPL-3)](https://tldrlegal.com/license/gnu-general-public-license-v3-(gpl-3)):
> You may copy, distribute and modify the software as long as you track changes/dates in source files. Any modifications to or software including (via compiler) GPL-licensed code must also be made available under the GPL along with build & install instructions.
parts and their libraries:
Copyright 2016 Accelerated Designs. All rights reserved.
